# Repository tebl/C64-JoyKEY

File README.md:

# C64 JoyKEY
The *C64 JoyKEY* was born out of the desire to build my own joystick, and after having a look at the various options available I chose to build one using Cherry MX keyboard switches. They are around a dollar per piece, so after getting it all to work properly on my beloved Commodore 64 I looked into using it with a whole selection of vintage computer systems as well. There are two main versions of the *C64 JoyKEY*, the keyboard-variant already described and a board designed for use with Sanwa arcade parts instead.

With options to handle multiple types of systems comes complexity, you'll have to make a few decisions on what you want out of the *C64 JoyKEY*. Do I only want to use it as a joystick replacement on vintage systems, ideally with 2-3 fire buttons where supported? If so, then you won't need the Arduino Pro Micro.

Want to use it on a modern system as a *WASD*-style keyboard or a gamepad, then install it - a common use of these types of devices is as a macro-keyboard or a stream-deck. Note that compared to many similar solutions, the microcontroller is not required for use with any of the vintage systems - the adapters actually follow the original circuit descriptions for controllers used with the actual vintage computers. What that means is that there is truly no chance of lag added by the controller. Ever.

The pictures below show the unit when connected to my Commodore 64, including the jumper settings used with it. As I've tried to keep things as close to the standard usually associated with Atari-style joysticks, there are two joystick connectors - this is because a lot of the Commodore 64 games supported using a second joystick for specific game functions.

As with most C64 games port 2 is the one to use, port 1 is just there to connect additional fire buttons. When in doubt, just connect a cable for port 2 and you should have a good time. This was labelled after the way the controller is used on the Commodore 64. 

## Getting one
I won't be selling these, so if you want one you will probably have to build it yourself (or call your favourite friend, ideally someone with a reasonable quality soldering iron). I've created a separate documents on [building](https://github.com/tebl/C64-JoyKEY/blob/main/documentation/building.md) a *C64 JoyKEY*, this is also where you'll find the [BOM](https://github.com/tebl/C64-JoyKEY/blob/main/documentation/building.md#bom) for this project (a list of needed parts and links to where PCBs can be ordered).

* [Building C64 JoyKEY](https://github.com/tebl/C64-JoyKEY/blob/main/documentation/building.md)
* [Building C64 JoyKEY Arcade](https://github.com/tebl/C64-JoyKEY/blob/main/documentation/building_arcade.md)
* [PCBWay shared projects](https://www.pcbway.com/project/shareproject/?tag=C64%20JoyKEY)

As with all things you're soldering together by yourself, the one who soldered it takes responsibility for it. I'll try answer any opened tickets as far as I am able, but know that this is a hobby-grade project and I might be busy on spending the little energy I have on other things (be patient, check out the [schematic](https://github.com/tebl/C64-JoyKEY/tree/main/documentation/schematic) while you wait).

## Setting it up
The *C64 JoyKEY* has a handful of jumpers that need to be set correctly in order to: A - function, B - not destroy your precious vintage computer and/or consoles. The necessary details have been put into a separate [configuration](https://github.com/tebl/C64-JoyKEY/blob/main/documentation/configuration.md)-document, check it out for some information on the systems I've attempted to use the *C64 JoyKEY* with.

* [Configuring C64 JoyKEY](https://github.com/tebl/C64-JoyKEY/blob/main/documentation/configuration.md)
* [Arduino firmware](https://github.com/tebl/C64-JoyKEY/blob/main/documentation/firmware.md)

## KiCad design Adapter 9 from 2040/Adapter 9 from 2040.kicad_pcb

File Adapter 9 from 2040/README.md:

# Adapter 9 from 2040
I cant really recall the entire list of adapters that I've made of the years, but there might actually have been a few more than 9 though this is definitely the first one that I've ended up calling *Adapter 9 from 2040*. Strikingly similar in function to the [C64 Joystick Adapter](https://github.com/tebl/C64-Joystick-Adapter) that I made a while back, but given my renewed interest in the *C64 JoyKEY* via [C64 JoyKEY 2040](https://github.com/tebl/C64-JoyKEY/tree/main/C64%20Joykey%202040) it made somewhat sense to create yet another "DB-9" to USB-controller adapter.

Except this time the implementation was based on [GP2040-CE](https://gp2040-ce.info), running on a Raspberry Pi Pico variant commonly referred to as the *RP2040-Zero*. At this point quite a lot of the older Arduino-libraries have hardly seen any features added to it, but as for *GP2040-CE* - if there's a feature that you can think of, then it's probably already there in some form or another. *Adapter 9 from 2040* in its most common setup presents itself to the system you connect it to as a wired *Xbox-360 Controller*, meaning that you can use it as a controller on quite a lot of different systems.

Personally I wanted it for use with the various releases from *Retro Games Ltd.* - great little systems for playing games on when I want something that should just work, but absolutely terrible controllers. I've tested it with *TheC64 Mini*, *TheA500 Mini* and most recently *TheSpectrum* to great effect, and being able to use my vintage joysticks with them only adds to the enjoyment.

- [1> Building the device](#1-building-the-device)
- [2> Schematic](#2-schematic)
- [3> BOM](#3-bom)

# 1> Building the device
Building the device should be a straight-forward affair, you just solder the meager selection of components into place. Pay particular attention to keeping the alignment of parts somewhat straight, that's pretty much it. This documentation was written with a board that looks like the following in mind, but note that the GitHub-repository might contain changes that have yet to be tested. For that reason it is recommended that PCBs are ordered directly from the PCBWay links provided in the BOM).

Before getting started on installing actual components there are a few things that we need to cover first, and that's setting up the various jumpers found on the back of the PCB. The ones towards the bottom covers the kind of signals we want to hook up to the "DB-9"-connector, and the only one that I recommend linking is *VCC_EN* as that will be needed for quite a few of the joysticks that include a turbo-function. Takes a little bit of practice to get these to link, but if you try and get the soldering iron to heat both pads simultaniously and keep feeding in solder you'll get a perfect blob before long.

The jumpers for *B2_EN* and *B3_EN* are for controllers that have one or two extra fire buttons with a commoned ground, but as these are quite rare I'd recommend that you leave these as they are unless you specifically know what you're doing. Or in the even rarer case, is the one where you're using either [C64 Arcade](https://github.com/tebl/C64-JoyKEY/tree/main/C64%20Arcade), [C64 JoyKEY](https://github.com/tebl/C64-JoyKEY/tree/main/C64%20Joykey) or the [C64 JoyKEY 2040](https://github.com/tebl/C64-JoyKEY/tree/main/C64%20Joykey%202040).

The one case where we really need to pay attention is the ones toward the middle of the PCB, these are needed in order to specify how your *0.96" I2C OLED*-display should be wired up. The reason is that when you're ordering these from various sources they'll send you displays that were made with differing pinouts, even more annoyingly is that often you'll look at the pictures to verify that you're getting a specific revision of it - but they'll just send you a different one. Here's what the one I've jumpered for in the above picture, note specifically that *GND* is on the first pin. That means that on both jumpers we need to link pins 1-2 together (with the tiny triangle indicating pin 1). If, on the other hand, the first pin had been labelled *VCC* (or quite possibly *VDD*) the you'd instead need to link pins 2-3 for both of the jumpers. 

Moving on to actualy components that we'll be installing, I always recommend that you install things in the order of their physical height. There's not all that much that can go wrong beyond making things harder for yourself to put this one together so don't overthink things. You will however need to decide if you'll be installing the *RP2040-Zero* development board directly to the board, or with pins between the two. Before all that though, we need to talk about what a *RP2040-Zero* actually is. And here's a couple of them that you might encounter while shopping around: 

Both of these are smaller versions of the *Raspberry Pi Pico* boards that come directly from the *Raspberry Pi Foundation*, but they're running the same chip so you essentially get the same amount of computational power - just with slightly less pins, and in a significantly smaller package. Confusingly this isn't a *Raspberry Pi* as the single-board computers (*SBC*) that came before it, this is a somewhat new line of microcontrollers similar to the *Arduino* or *ESP-32*. As for the boards above, the first one is from a vendor called *Waveshare* and this is the version that you'll encounter on more reputed sites for purchasing electrical components. The other is a clone that normally works just as well, just at half the price and without any expectation that all of were put together like they should - so buy at least two of them in case one blows up!

Here I've skipped over the difficult parts and soldered it into place. In order to get the alignment just right I tend to insert pin headers through both boards on at least two of the sides, then position it just right and solder one pin into place. If it all looks right, you can go ahead and remove the pin headers before soldering the rest. It might take some getting used to soldering things together like this if you're not used to it, but just try and get the soldering iron to touch both pads at the same time then feed in the solder until it forms a shiny avalanche.

If you're going to install a faceplate on the adapter, then you're going to need a set of standoffs in each of the four corners. These need to have a height of 6mm, they're fixed in place with similar nuts on the underside. You might also use some that are slightly longer, but keep in mind that we need to have enough of a reach on the pin headers on your OLED to match - switches also need to be tall enough to poke through all of it. On second thought, just go with 6mm and we'll move on from there.

Next up is the *right-angle "DB-9" male connector* that I keep buying off of the regular sites, and I believe it's a clone of an RND-part, but don't hold me to that. If you look for the a connector that looks like this on the pictures, then you'll get the correct one. It snaps into place on the board and solders in well enough, just keep your fingers away from the metal as it heats up quite quickly when soldering. I've literally burned myself on them several times. And at the time of writing, this is probably the first time I've used the word "literally" correctly. I hope. 

The next step is all of the switches, and here I've inserted them all into place and temporarily installed the faceplate. Doing it in this order ensures that the switch ends up sitting correctly, and won't be rubbing too much against the cutouts in the faceplate. Once satisfied with all of that, you can go ahead and solder in the switches. Just do one of the pins at first, then recheck to make sure it hasn't popped out or gone wonky on you in the meantime (ask me how I know).

As for my next trick on my list of things I've just done without much to actually show you, I've gone ahead and added the display. Previously on this episode of putting things together with our fiery stick of endless ouchies (also known as a soldering iron), we lamented the state lack of real part numbers for things like displays. Clones taking liberties when shamelessly copying other clones, enabling people like me to actually own a whole bunch of them and so on. The board will take just about any *0.96" I2C OLED*-display, but you'll need to ensure that you order specific ones if you want the cutouts on the faceplates to line up just perfectly. Currently there is only one available, [FaceplateB](https://github.com/tebl/C64-JoyKEY/tree/main/faceplates/Adapter%209%20FaceplateB) - this one was designed for the *New* displays available in all the usual places. Technically it's actually the new *New* display, but who's counting - at least one identifying trait is that they're the first generation that came with yellow as colour.

There are holes for orienting it correctly, but before even considering soldering anything - take a look at how it looks with the faceplate in place. We need to ensure that it sits flush against the inside edge of the faceplate, and while you could glue the foam that often comes around the pins directly to the PCB to push it upwards - I prefer adding a bunch of layers of double-sided foam tape. Just don't go overboard -  we want it to push the glass up against the PCB, not shatter the whole thing from extreme pressure. If you need to reorient it a bit, you can poke a screwdriver into the mounting holes from the back and adjust it that way. Once satisfied with your rough placement, solder a single pin. Recheck. Recheck. Recheck. And then solder the rest.

Once satisfied with all of it, make yourself a cup of tea, soup or whatever you want - you're buying anyway! Once back to the table, you need to take the faceplate back off again, as we need access to the buttons directly on the *RP2040-Zero* when installing *GP2040-CE*, but that's all covered in a completely different document - [From Zero to GP2040](https://github.com/tebl/C64-JoyKEY/blob/main/documentation/gp2040_zero.md).

# 2> Schematic
The supplied KiCad files should be sufficient as both a schematic and as a  starting point for ordering PCBs (basically you could just zip the contents of the export folder and upload that on a fabrication site), the schematic is also available in [PDF-format](https://github.com/tebl/C64-JoyKEY/tree/main/documentation/schematic) and this is what you'll need to print and work your way through when things fail to work as expected.

# 3> BOM
Most parts should be easy to get a hold of from all of the regular places, just not any of the incredibly reputable ones. Which is why things usually cost a third of what they cost elsewhere, but you need to buy two in order to ensure that at least one works. I get most of my components from AliExpress though I hear nice things about the wheel of fortune thingie, but they sent one too many notifications so they're banned in my household.

I'd really like for you to have a nice and clear BOM with consistent part numbers from actual reputable sites, but I can't even afford their shipping options so it is what it is - mostly hints at what to search for and how many you need. If a counted part is listed in a parenthesis, then you don't strictly need that part though it's all cheap enough that you probably count on buying them anyway.

| Reference        | Item                                                              | Count | Order  |
| -----------------| ----------------------------------------------------------------- | ----- | ------ |
| PCB              | Fabricate using Gerber files                                      |     1 | [PCBWay](https://www.pcbway.com/project/shareproject/Adapter_9_from_2040_578739f8.html)
| PCB (Faceplate B)| Fabricate using Gerber files                                      |    (1)| [PCBWay](https://www.pcbway.com/project/shareproject/Adapter_9_from_2040_Faceplate_B_dc748e4f.html)
| IC1 *            | 0.96" I2C OLED display 128x64 (New variant reqd. for FaceplateB)) |    (1)|
| J1               | Male DB-9 right-angle connector (usually listed as PCB-mount)     |     1 |
| SW1-SW8          | 6x6x10mm tactile switch ("DIP-4")                                 |    (8)|
| U1               | Raspberry Pi Pico (RP2040-Zero)                                   |     1 |
| **               | M3 nylon nut                                                      |    (4)|
| **               | M3x6+6mm nylon hex standoff                                       |    (4)|
| **               | M3x6mm nylon screw                                                |    (4)|

*) See text for construction for hints on purchasing the correct variant to go with a specific faceplate, when in doubt order several and use the one that fits.

**) These components are for the additional faceplate. Strictly not necessary, but keeps the  whole setup looking as stylish as it can be. The faceplate is reversible, so install it in the orientation that you'd like.

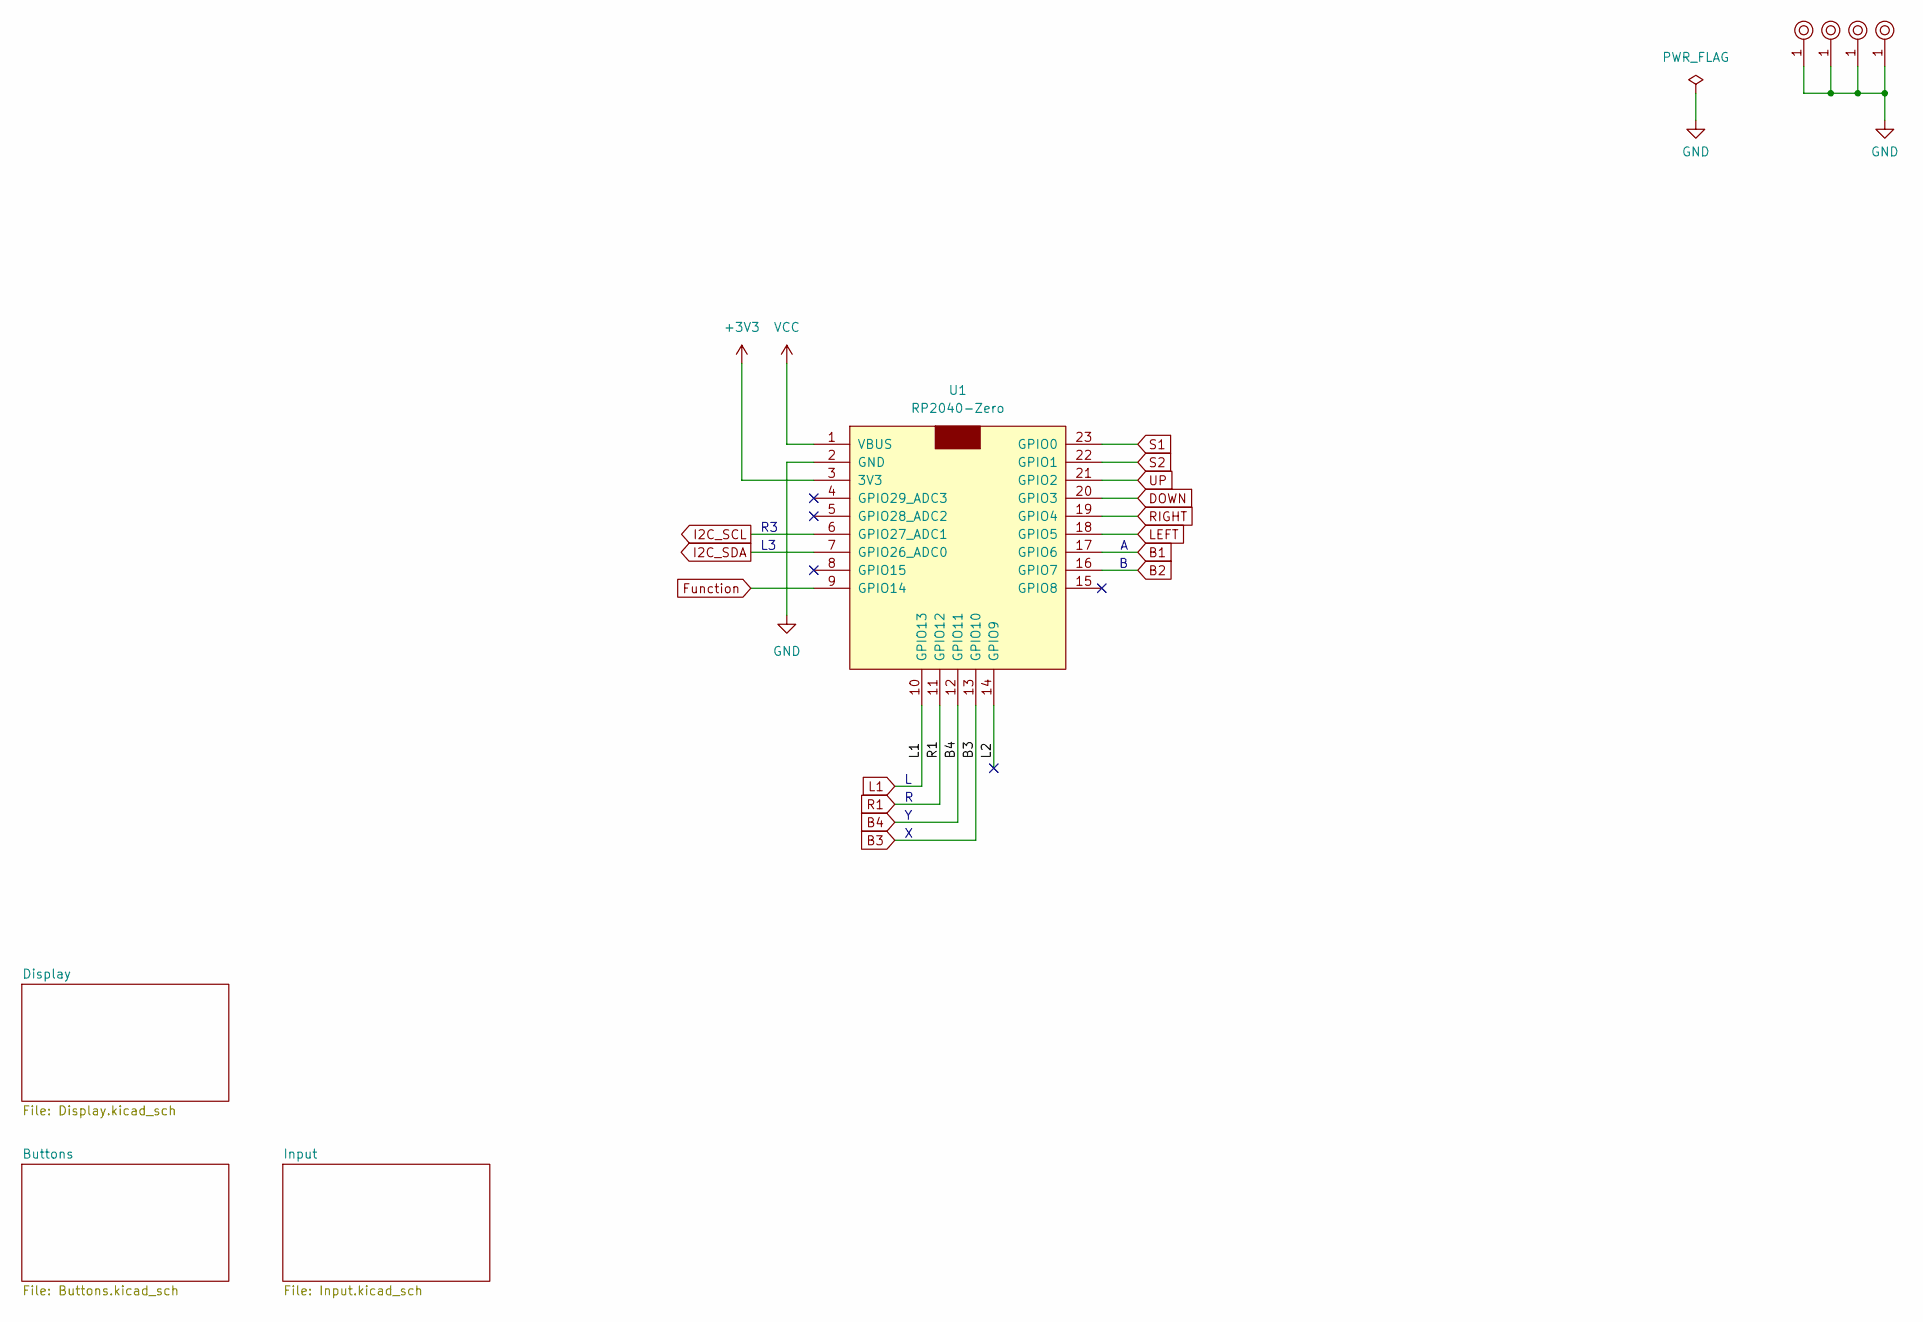
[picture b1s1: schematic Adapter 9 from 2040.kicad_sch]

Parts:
M1, M2, M3, M4: Mounting; M3_pin
U1: RP2040-Zero; RP2040-Zero_Clean

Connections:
+3V3: U1.3 (3V3); also elsewhere on the board
/L2: U1.14 (GPIO9)
/L2_1: U1.14 (GPIO9)
B1: U1.17 (GPIO6); also elsewhere on the board
B2: U1.16 (GPIO7); also elsewhere on the board
B3: U1.13 (GPIO10); also elsewhere on the board
B4: U1.12 (GPIO11); also elsewhere on the board
DOWN: U1.20 (GPIO3); also elsewhere on the board
Function: U1.9 (GPIO14); also elsewhere on the board
GND: M1.1, M2.1, M3.1, M4.1, U1.2 (GND); also elsewhere on the board
I2C_SCL: U1.6 (GPIO27_ADC1); also elsewhere on the board
I2C_SDA: U1.7 (GPIO26_ADC0); also elsewhere on the board
L1: U1.10 (GPIO13); also elsewhere on the board
LEFT: U1.18 (GPIO5); also elsewhere on the board
R1: U1.11 (GPIO12); also elsewhere on the board
RIGHT: U1.19 (GPIO4); also elsewhere on the board
S1: U1.23 (GPIO0); also elsewhere on the board
S2: U1.22 (GPIO1); also elsewhere on the board
UP: U1.21 (GPIO2); also elsewhere on the board
VCC: U1.1 (VBUS); also elsewhere on the board

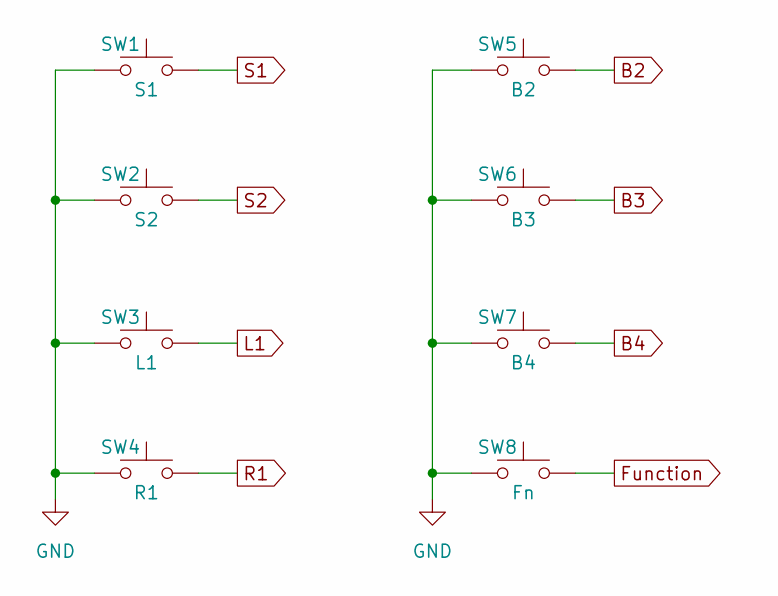
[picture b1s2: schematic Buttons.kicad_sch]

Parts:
SW1: S1; SW_PUSH_6mm
SW2: S2; SW_PUSH_6mm
SW3: L1; SW_PUSH_6mm
SW4: R1; SW_PUSH_6mm
SW5: B2; SW_PUSH_6mm
SW6: B3; SW_PUSH_6mm
SW7: B4; SW_PUSH_6mm
SW8: Fn; SW_PUSH_6mm

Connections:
B2: SW5.1; also elsewhere on the board
B3: SW6.1; also elsewhere on the board
B4: SW7.1; also elsewhere on the board
Function: SW8.1; also elsewhere on the board
GND: SW1.2, SW2.2, SW3.2, SW4.2, SW5.2, SW6.2, SW7.2, SW8.2; also elsewhere on the board
L1: SW3.1; also elsewhere on the board
R1: SW4.1; also elsewhere on the board
S1: SW1.1; also elsewhere on the board
S2: SW2.1; also elsewhere on the board

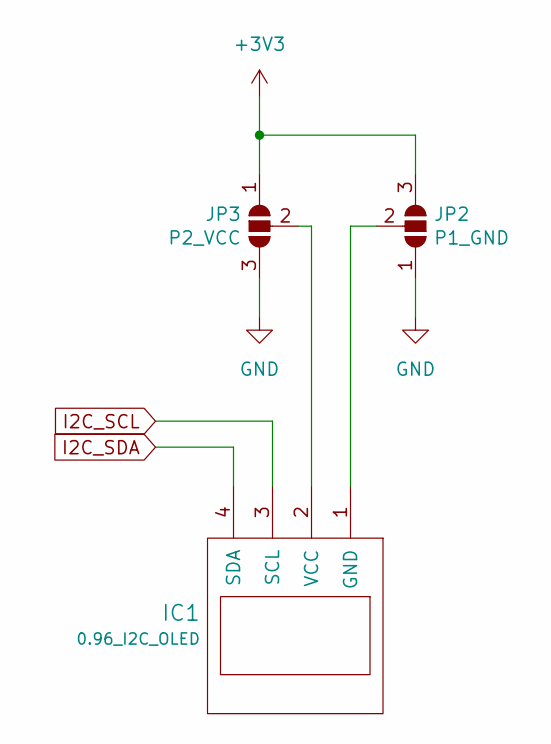
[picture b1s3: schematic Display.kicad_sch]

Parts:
IC1: 0.96_I2C_OLED; 0.96_I2C_OLED_NEW_Top
JP2: P1_GND; SolderJumper-3_P1.3mm_Open_Pad1.0x1.5mm
JP3: P2_VCC; SolderJumper-3_P1.3mm_Open_Pad1.0x1.5mm

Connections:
+3V3: JP2.3 (B), JP3.1 (A); also elsewhere on the board
GND: JP2.1 (A), JP3.3 (B); also elsewhere on the board
I2C_SCL: IC1.3 (SCL); also elsewhere on the board
I2C_SDA: IC1.4 (SDA); also elsewhere on the board
unnamed: IC1.1 (GND), JP2.2 (C)
unnamed: IC1.2 (VCC), JP3.2 (C)

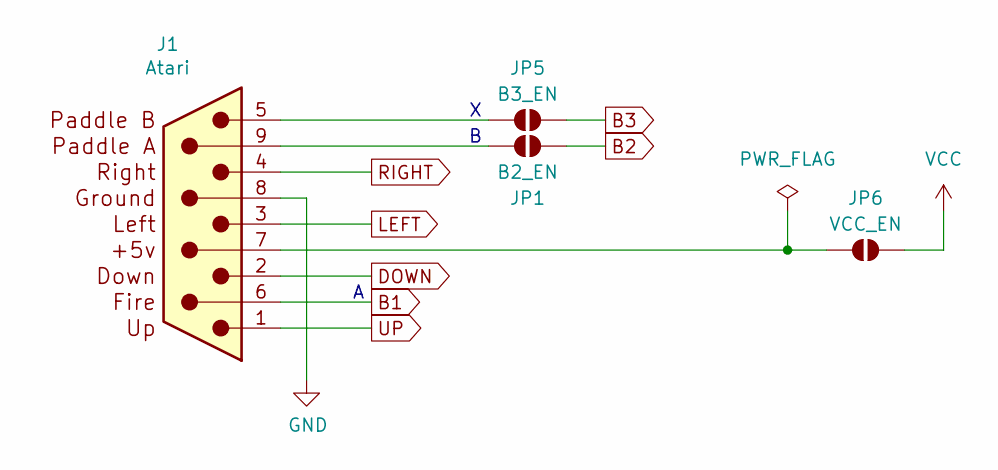
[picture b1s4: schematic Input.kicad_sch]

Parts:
J1: Atari; DSUB-9_Male_Horizontal_P2.77x2.84mm_EdgePinOffset7.70mm_Hou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
JP1: B2_EN; bridge
JP5: B3_EN; bridge
JP6: VCC_EN; bridge

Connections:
B1: J1.6; also elsewhere on the board
B2: JP1.2 (B); also elsewhere on the board
B3: JP5.2 (B); also elsewhere on the board
DOWN: J1.2; also elsewhere on the board
GND: J1.8 (GND); also elsewhere on the board
LEFT: J1.3; also elsewhere on the board
unnamed: J1.7 (VCC), JP6.1 (A)
unnamed: J1.9, JP1.1 (A)
unnamed: J1.5, JP5.1 (A)
RIGHT: J1.4; also elsewhere on the board
UP: J1.1; also elsewhere on the board
VCC: JP6.2 (B); also elsewhere on the board

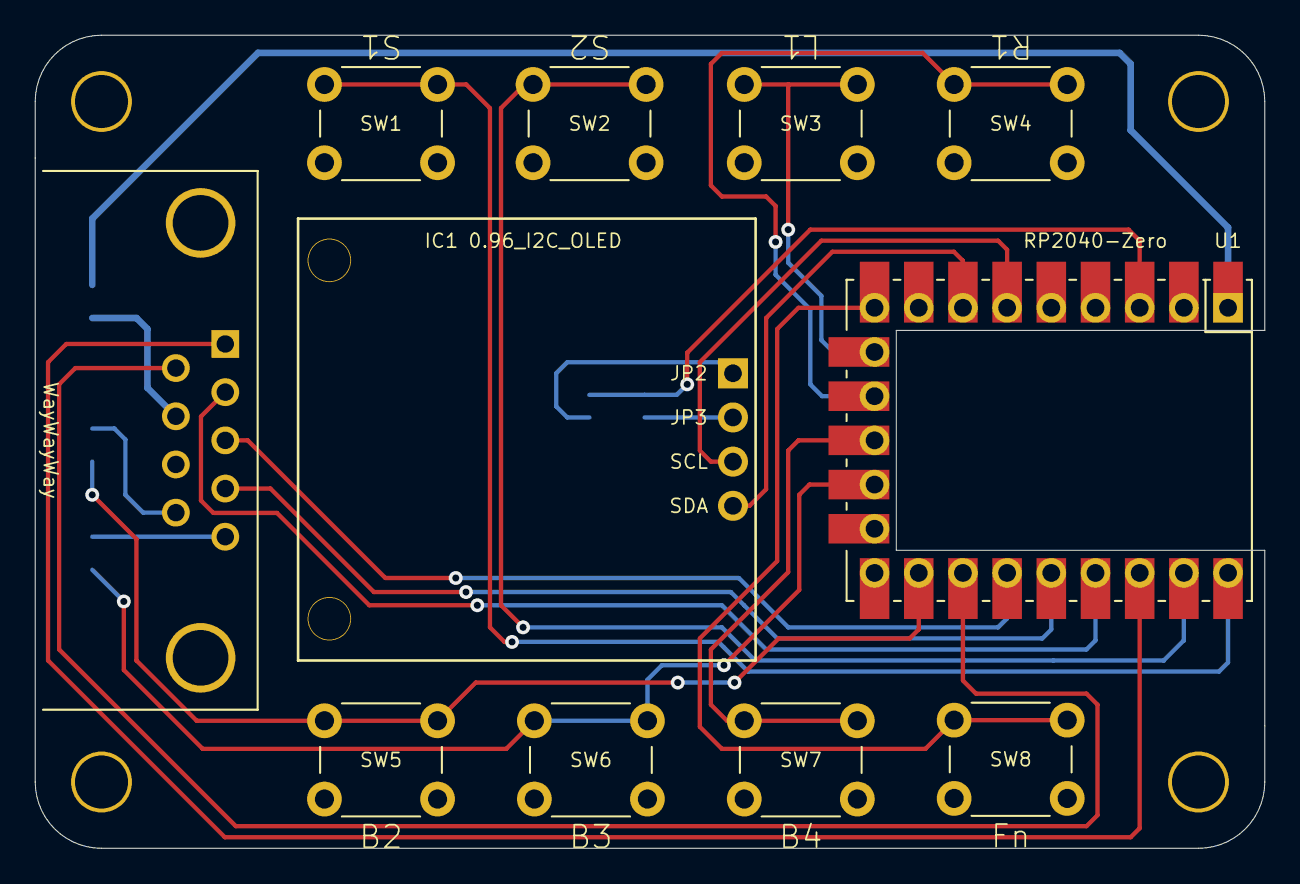
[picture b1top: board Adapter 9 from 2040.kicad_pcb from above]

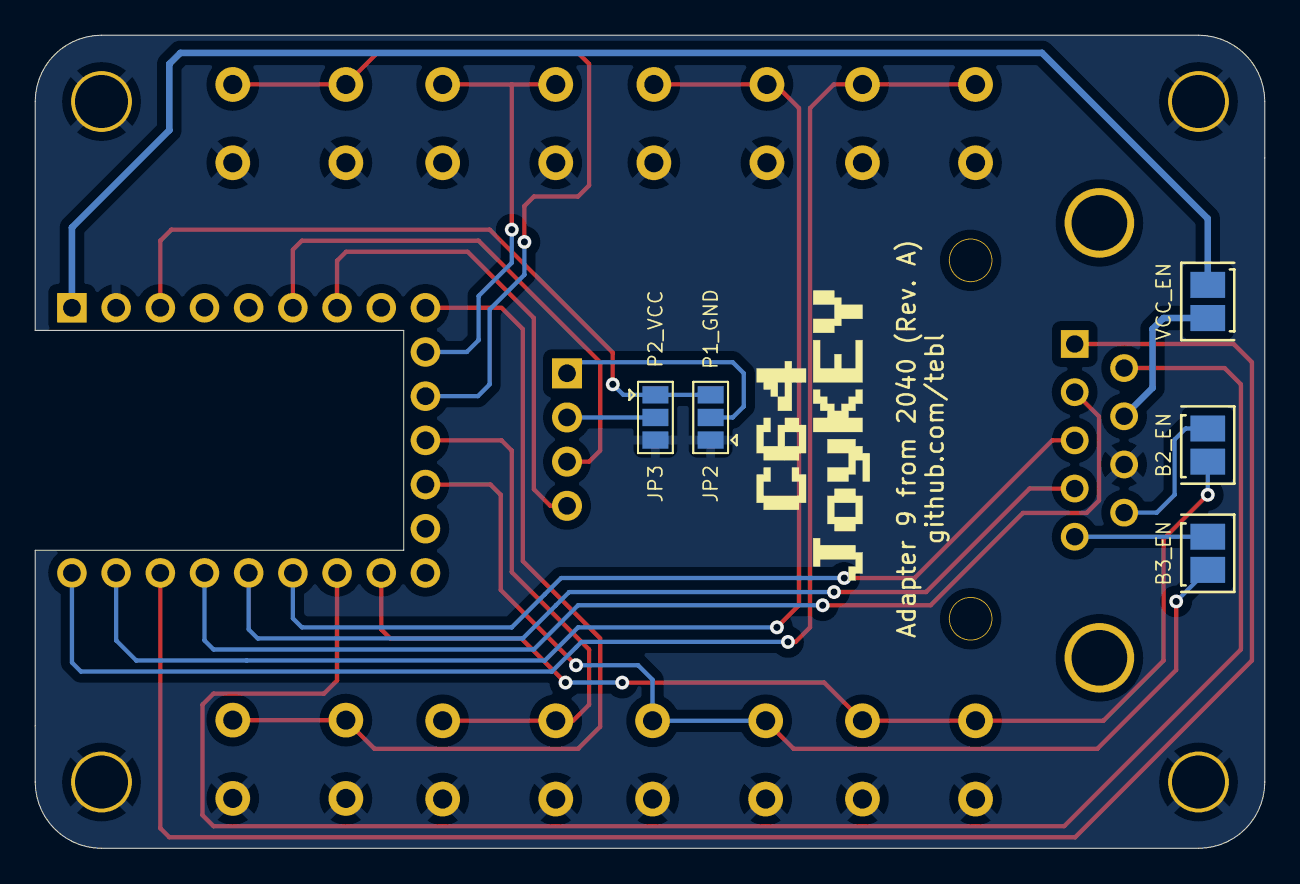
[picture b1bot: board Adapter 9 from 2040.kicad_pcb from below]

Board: 2 copper layers, 70.7 x 46.7 mm, 20 parts (5 on the bottom side), 23 nets.

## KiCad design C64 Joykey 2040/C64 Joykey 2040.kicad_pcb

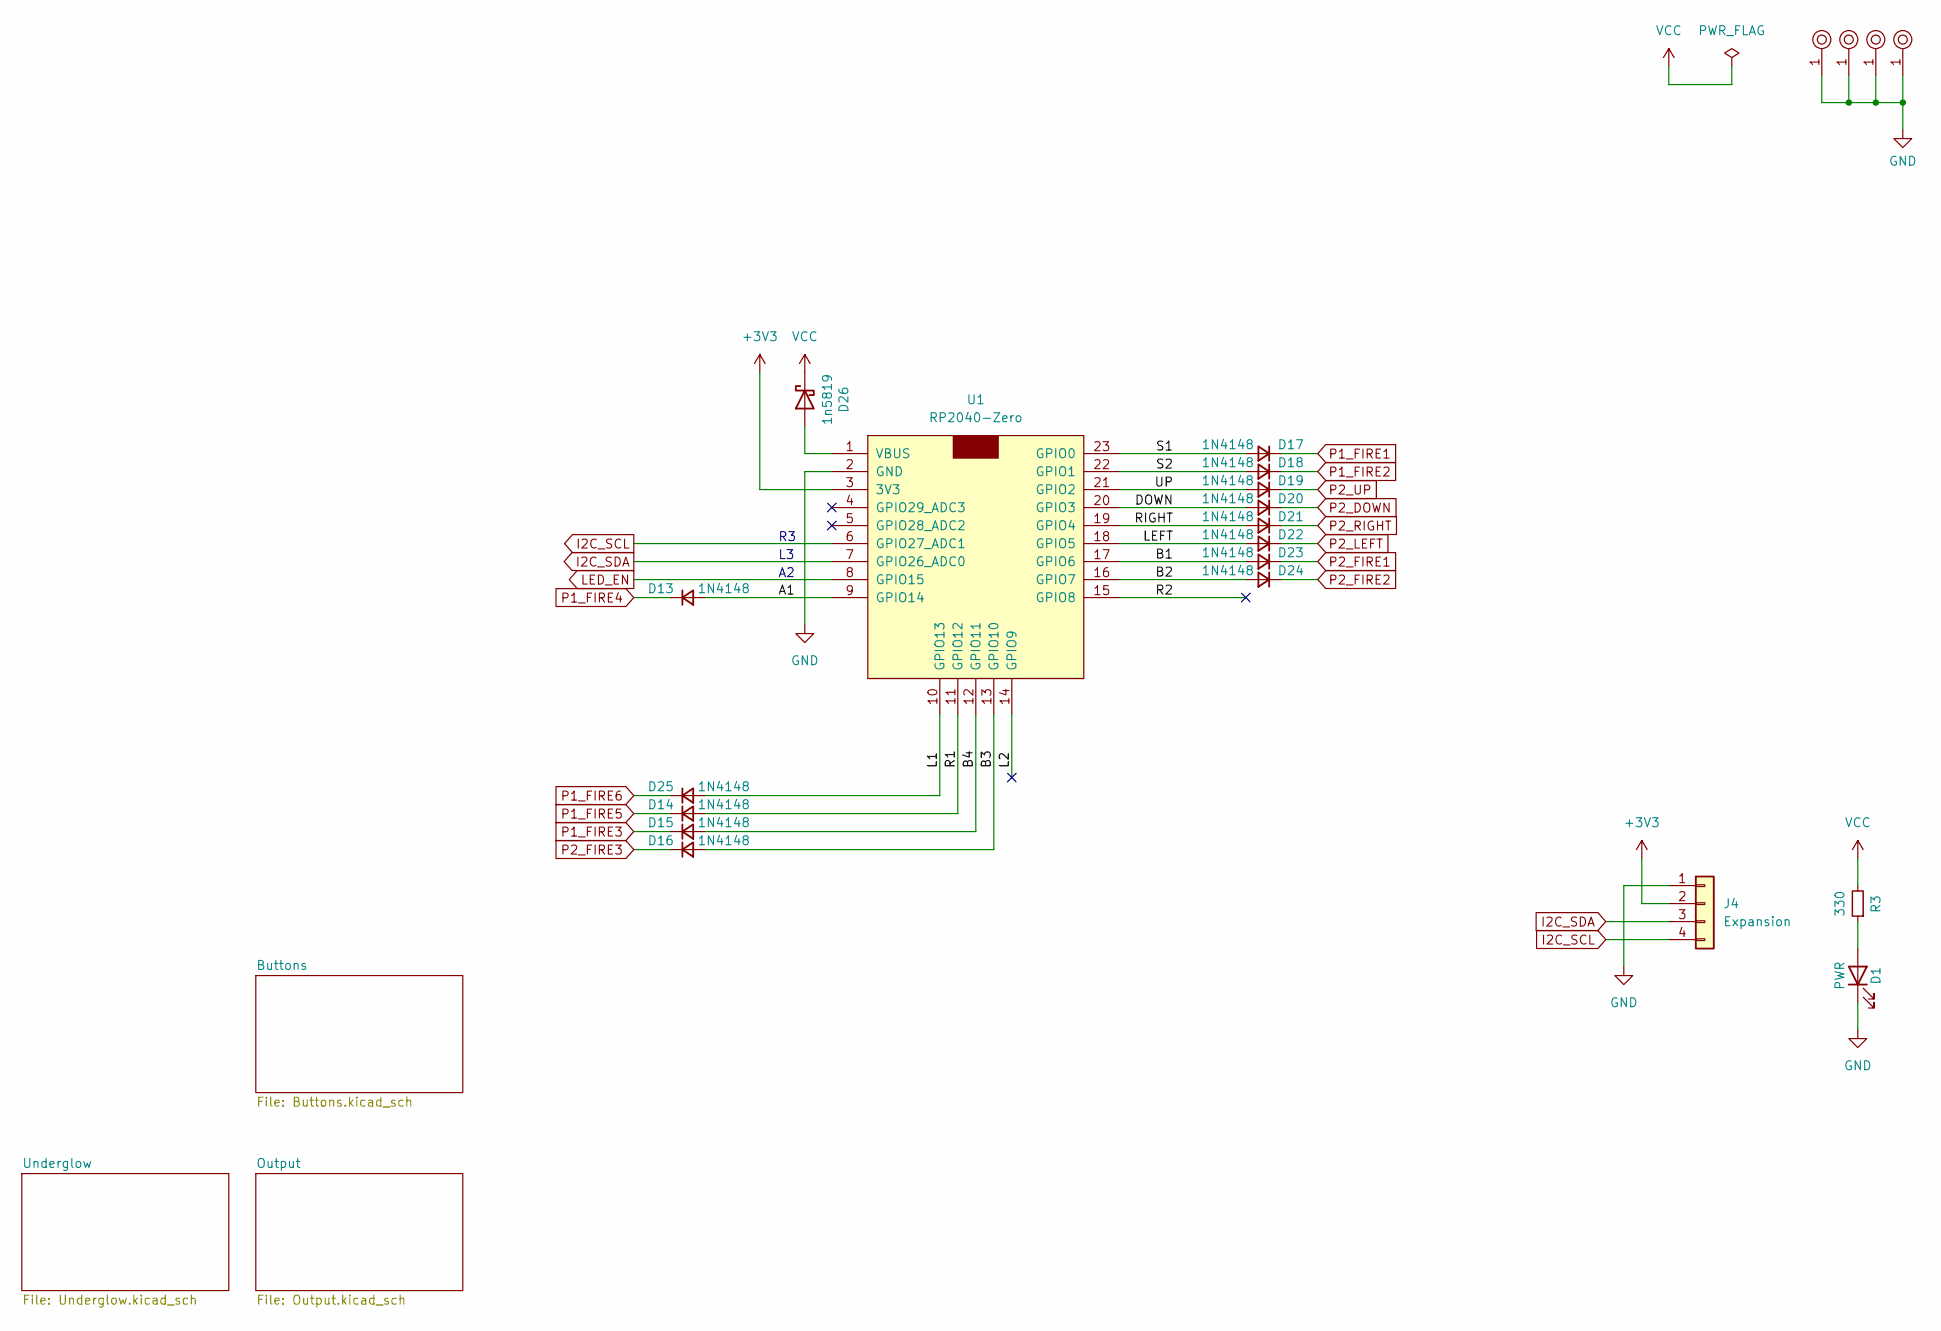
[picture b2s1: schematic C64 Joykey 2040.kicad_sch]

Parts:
D1: PWR; LED_D5.0mm
D13, D14, D15, D16, D17, D18, D19, D20, D21, D22, D23, D24, D25: 1N4148; D_DO-35_SOD27_P7.62mm_Horizontal
D26: 1n5819; D_DO-41_SOD81_P10.16mm_Horizontal
J4: Expansion; JST_XH_B4B-XH-A_1x04_P2.50mm_Right_Angle
M1, M2, M3, M4: Mounting; M3_pin
R3: 330; R_Axial_DIN0207_L6.3mm_D2.5mm_P10.16mm_Horizontal
U1: RP2040-Zero; RP2040-Zero-THT

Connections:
+3V3: J4.2, U1.3 (3V3)
/A1: D13.2 (A), U1.9 (GPIO14)
/B1: D23.2 (A), U1.17 (GPIO6)
/B2: D24.2 (A), U1.16 (GPIO7)
/B3: D16.2 (A), U1.13 (GPIO10)
/B4: D15.2 (A), U1.12 (GPIO11)
/DOWN: D20.2 (A), U1.20 (GPIO3)
/L1: D25.2 (A), U1.10 (GPIO13)
/L2: U1.14 (GPIO9)
/LEFT: D22.2 (A), U1.18 (GPIO5)
/R1: D14.2 (A), U1.11 (GPIO12)
/R2: U1.15 (GPIO8)
/RIGHT: D21.2 (A), U1.19 (GPIO4)
/S1: D17.2 (A), U1.23 (GPIO0)
/S2: D18.2 (A), U1.22 (GPIO1)
/UP: D19.2 (A), U1.21 (GPIO2)
GND: D1.1 (K), J4.1, M1.1, M2.1, M3.1, M4.1, U1.2 (GND); also elsewhere on the board
I2C_SCL: J4.4, U1.6 (GPIO27_ADC1)
I2C_SDA: J4.3, U1.7 (GPIO26_ADC0)
LED_EN: U1.8 (GPIO15); also elsewhere on the board
unnamed: D1.2 (A), R3.1
unnamed: D26.2 (A), U1.1 (VBUS)
P1_FIRE1: D17.1 (K); also elsewhere on the board
P1_FIRE2: D18.1 (K); also elsewhere on the board
P1_FIRE3: D15.1 (K); also elsewhere on the board
P1_FIRE4: D13.1 (K); also elsewhere on the board
P1_FIRE5: D14.1 (K); also elsewhere on the board
P1_FIRE6: D25.1 (K); also elsewhere on the board
P2_DOWN: D20.1 (K); also elsewhere on the board
P2_FIRE1: D23.1 (K); also elsewhere on the board
P2_FIRE2: D24.1 (K); also elsewhere on the board
P2_FIRE3: D16.1 (K); also elsewhere on the board
P2_LEFT: D22.1 (K); also elsewhere on the board
P2_RIGHT: D21.1 (K); also elsewhere on the board
P2_UP: D19.1 (K); also elsewhere on the board
VCC: D26.1 (K), R3.2; also elsewhere on the board

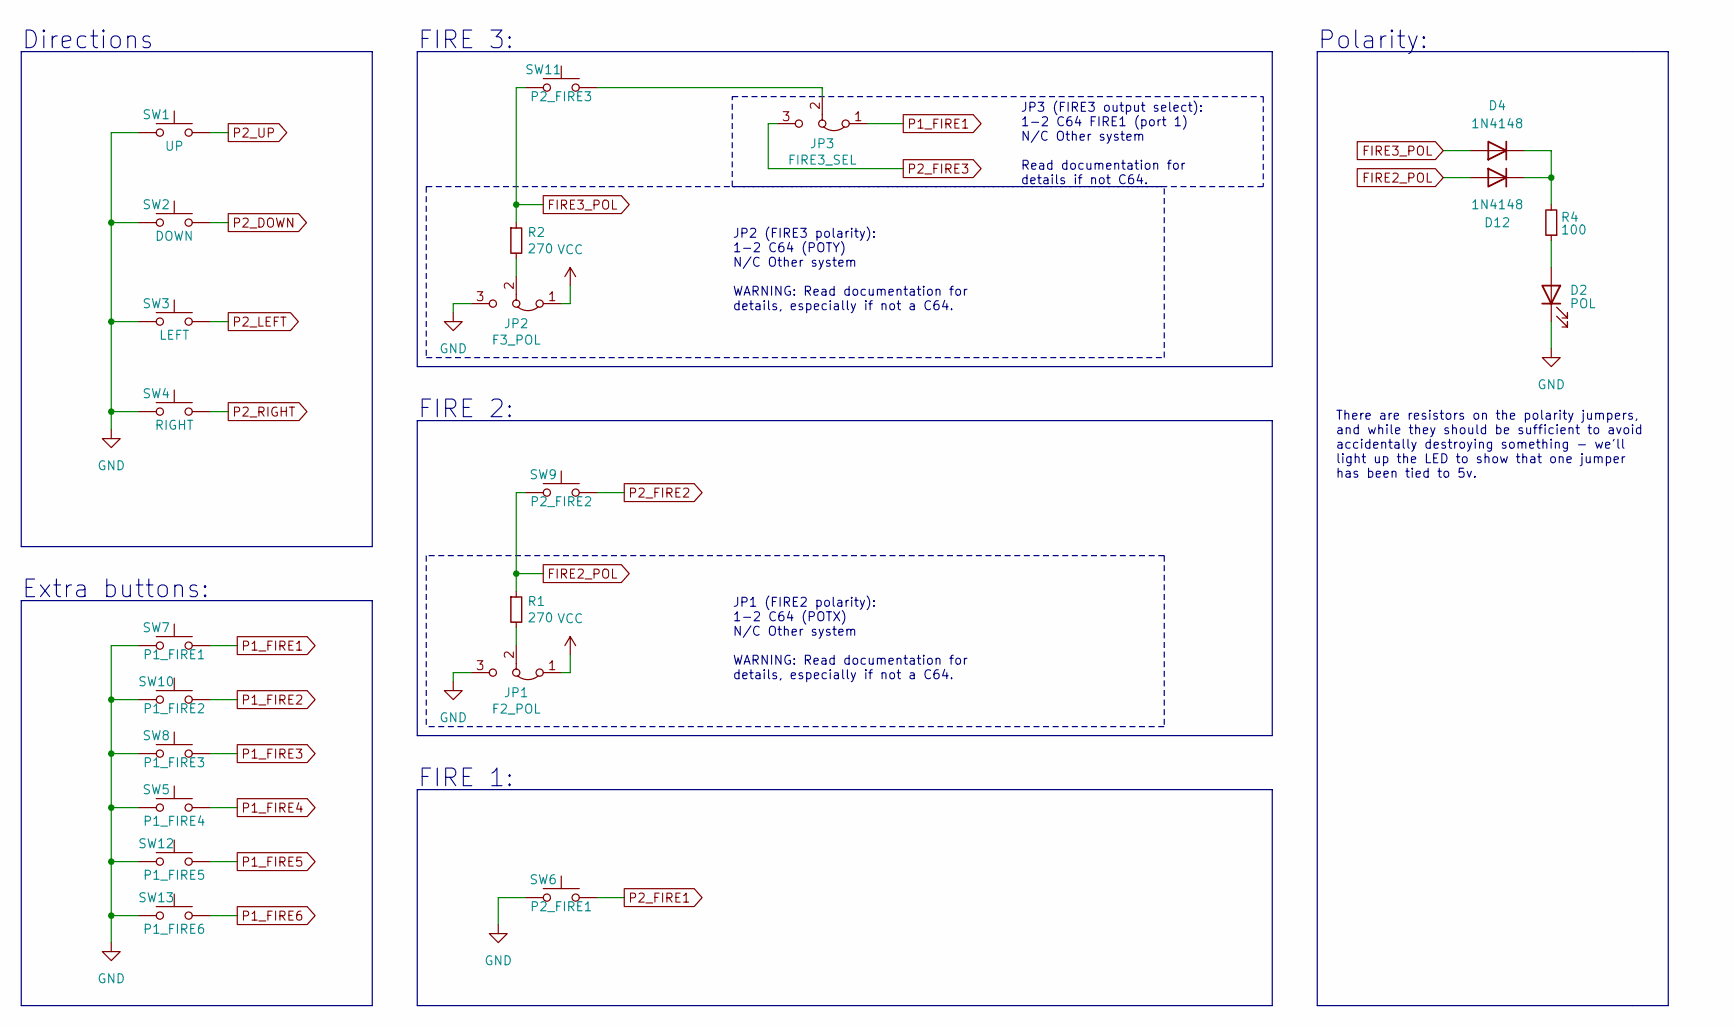
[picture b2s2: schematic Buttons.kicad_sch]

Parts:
D2: POL; LED_D5.0mm
D4, D12: 1N4148; D_DO-35_SOD27_P7.62mm_Horizontal
JP1: F2_POL; PinHeader_1x03_P2.54mm_Horizontal
JP2: F3_POL; PinHeader_1x03_P2.54mm_Horizontal
JP3: FIRE3_SEL; PinHeader_1x03_P2.54mm_Horizontal
R1, R2: 270; R_Axial_DIN0207_L6.3mm_D2.5mm_P10.16mm_Horizontal
R4: 100; R_Axial_DIN0207_L6.3mm_D2.5mm_P10.16mm_Horizontal
SW1: UP; SW_Cherry_MX_1.00u_PCB
SW2: DOWN; SW_Cherry_MX_1.00u_PCB
SW3: LEFT; SW_Cherry_MX_1.00u_PCB
SW4: RIGHT; SW_Cherry_MX_1.00u_PCB
SW5: P1_FIRE4; SW_Tactile_SPST_Angled_PTS645Vx31-2LFS
SW6: P2_FIRE1; SW_Cherry_MX_1.00u_PCB
SW7: P1_FIRE1; SW_Tactile_SPST_Angled_PTS645Vx31-2LFS
SW8: P1_FIRE3; SW_Tactile_SPST_Angled_PTS645Vx31-2LFS
SW9: P2_FIRE2; SW_Cherry_MX_1.00u_PCB
SW10: P1_FIRE2; SW_Tactile_SPST_Angled_PTS645Vx31-2LFS
SW11: P2_FIRE3; SW_Cherry_MX_1.00u_PCB
SW12: P1_FIRE5; SW_Tactile_SPST_Angled_PTS645Vx31-2LFS
SW13: P1_FIRE6; SW_Tactile_SPST_Angled_PTS645Vx31-2LFS

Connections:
FIRE2_POL: D12.2 (A), R1.1, SW9.2
FIRE3_POL: D4.2 (A), R2.1, SW11.2
GND: D2.1 (K), JP1.3 (B), JP2.3 (B), SW1.2, SW2.2, SW3.2, SW4.2, SW5.2, SW6.2, SW7.2, SW8.2, SW10.2, SW12.2, SW13.2; also elsewhere on the board
unnamed: D2.2 (A), R4.1
unnamed: D4.1 (K), D12.1 (K), R4.2
unnamed: JP1.2 (C), R1.2
unnamed: JP2.2 (C), R2.2
unnamed: JP3.2 (C), SW11.1
P1_FIRE1: JP3.1 (A), SW7.1; also elsewhere on the board
P1_FIRE2: SW10.1; also elsewhere on the board
P1_FIRE3: SW8.1; also elsewhere on the board
P1_FIRE4: SW5.1; also elsewhere on the board
P1_FIRE5: SW12.1; also elsewhere on the board
P1_FIRE6: SW13.1; also elsewhere on the board
P2_DOWN: SW2.1; also elsewhere on the board
P2_FIRE1: SW6.1; also elsewhere on the board
P2_FIRE2: SW9.1; also elsewhere on the board
P2_FIRE3: JP3.3 (B); also elsewhere on the board
P2_LEFT: SW3.1; also elsewhere on the board
P2_RIGHT: SW4.1; also elsewhere on the board
P2_UP: SW1.1; also elsewhere on the board
VCC: JP1.1 (A), JP2.1 (A); also elsewhere on the board

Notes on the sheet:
FIRE 1:
JP2 (FIRE3 polarity): 1-2 C64 (POTY) N/C Other system WARNING: Read documentation for details, especially if not a C64.
There are resistors on the polarity jumpers, and while they should be sufficient to avoid accidentally destroying something - we'll light up the LED to show that one jumper has been tied to 5v.
JP1 (FIRE2 polarity): 1-2 C64 (POTX) N/C Other system WARNING: Read documentation for details, especially if not a C64.
Directions
FIRE 3:
Extra buttons:
FIRE 2:
Polarity:
JP3 (FIRE3 output select): 1-2 C64 FIRE1 (port 1) N/C Other system Read documentation for details if not C64.

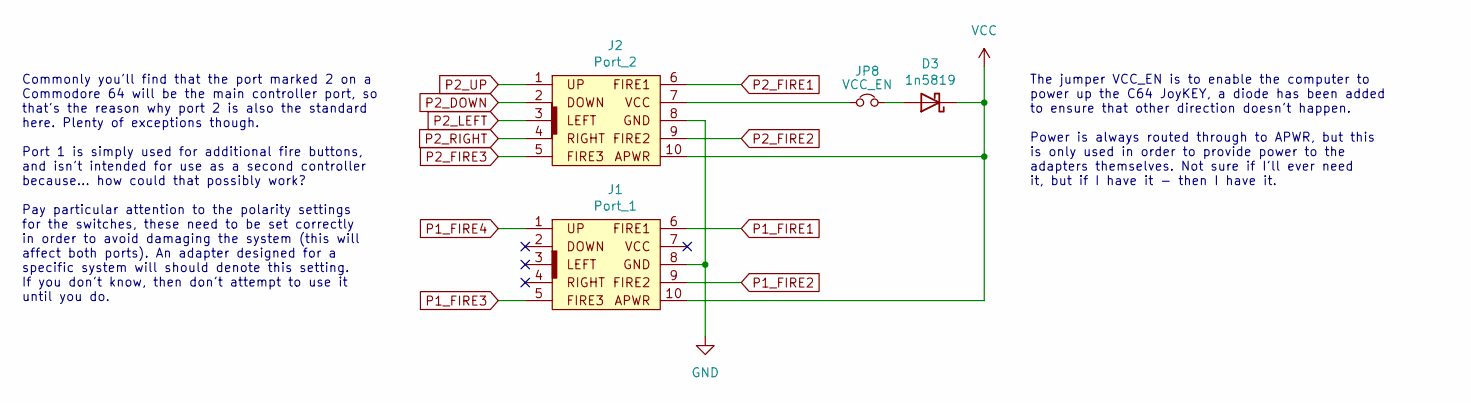
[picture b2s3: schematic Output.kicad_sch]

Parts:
D3: 1n5819; D_DO-41_SOD81_P10.16mm_Horizontal
J1: Port_1; IDC_Joystick
J2: Port_2; IDC_Joystick
JP8: VCC_EN; PinHeader_1x02_P2.54mm_Vertical

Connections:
GND: J1.8, J2.8; also elsewhere on the board
unnamed: D3.2 (A), JP8.2
unnamed: J2.7, JP8.1
P1_FIRE1: J1.6; also elsewhere on the board
P1_FIRE2: J1.9; also elsewhere on the board
P1_FIRE3: J1.5; also elsewhere on the board
P1_FIRE4: J1.1; also elsewhere on the board
P2_DOWN: J2.2; also elsewhere on the board
P2_FIRE1: J2.6; also elsewhere on the board
P2_FIRE2: J2.9; also elsewhere on the board
P2_FIRE3: J2.5; also elsewhere on the board
P2_LEFT: J2.3; also elsewhere on the board
P2_RIGHT: J2.4; also elsewhere on the board
P2_UP: J2.1; also elsewhere on the board
VCC: D3.1 (K), J1.10 (EX_VCC), J2.10 (EX_VCC); also elsewhere on the board

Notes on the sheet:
Commonly you'll find that the port marked 2 on a Commodore 64 will be the main controller port, so that's the reason why port 2 is also the standard here. Plenty of exceptions though. Port 1 is simply used for additional fire buttons, and isn't intended for use as a second controller because... how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
The jumper VCC_EN is to enable the computer to power up the C64 JoyKEY, a diode has been added to ensure that other direction doesn't happen. Power is always routed through to APWR, but this is only used in order to provide power to the adapters themselves. Not sure if I'll ever need it, but if I h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

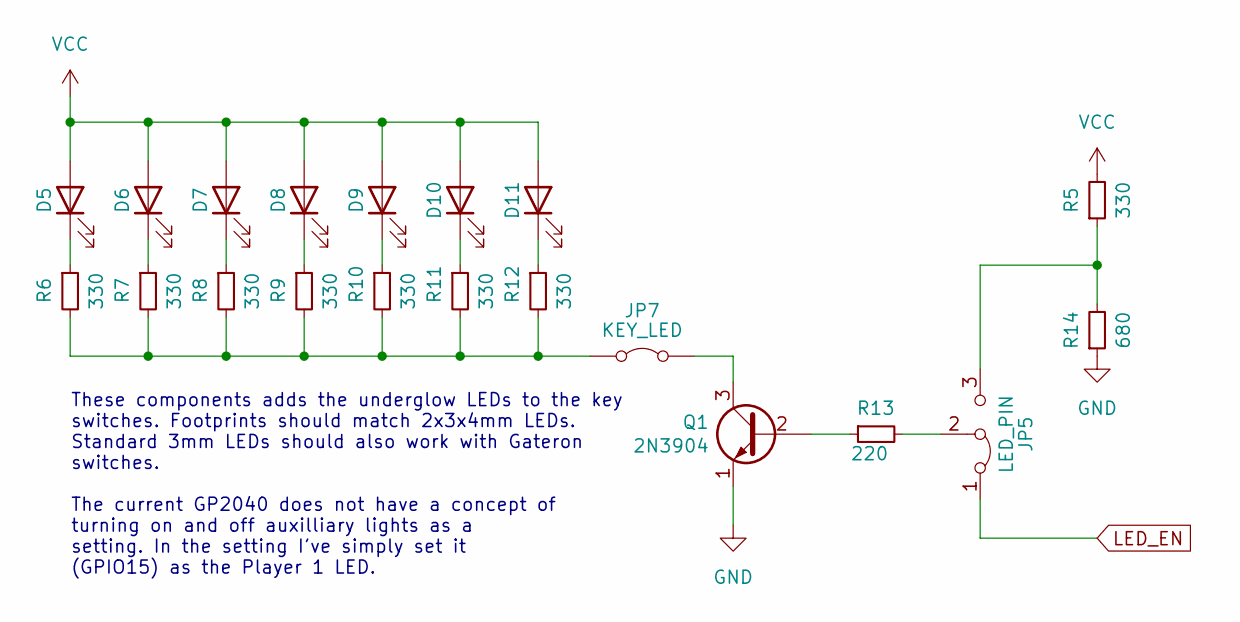
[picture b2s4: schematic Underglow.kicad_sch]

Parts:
D5, D6, D7, D8, D9, D10, D11: LED; LED_Rectangular_W3.0mm_H2.0mm
JP5: LED_PIN; PinHeader_1x03_P2.54mm_Vertical
JP7: KEY_LED; PinHeader_1x02_P2.54mm_Horizontal
Q1: 2N3904; TO-92_Inline_Wide
R5, R6, R7, R8, R9, R10, R11, R12: 330; R_Axial_DIN0207_L6.3mm_D2.5mm_P10.16mm_Horizontal
R13: 220; R_Axial_DIN0207_L6.3mm_D2.5mm_P10.16mm_Horizontal
R14: 680; R_Axial_DIN0207_L6.3mm_D2.5mm_P10.16mm_Horizontal

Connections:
GND: Q1.1 (E), R14.1; also elsewhere on the board
LED_EN: JP5.1 (A); also elsewhere on the board
unnamed: D5.1 (K), R6.1
unnamed: D6.1 (K), R7.1
unnamed: D7.1 (K), R8.1
unnamed: D8.1 (K), R9.1
unnamed: D9.1 (K), R10.1
unnamed: D10.1 (K), R11.1
unnamed: D11.1 (K), R12.1
unnamed: JP5.3 (B), R5.1, R14.2
unnamed: JP5.2 (C), R13.2
unnamed: JP7.1 (A), R6.2, R7.2, R8.2, R9.2, R10.2, R11.2, R12.2
unnamed: JP7.2 (B), Q1.3 (C)
unnamed: Q1.2 (B), R13.1
VCC: D5.2 (A), D6.2 (A), D7.2 (A), D8.2 (A), D9.2 (A), D10.2 (A), D11.2 (A), R5.2; also elsewhere on the board

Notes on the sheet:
These components adds the underglow LEDs to the key switches. Footprints should match 2x3x4mm LEDs. Standard 3mm LEDs should also work with Gateron switches. The current GP2040 does not have a concept of turning on and off auxilliary lights as a setting. In the setting I've simply set it (GPIO15) a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

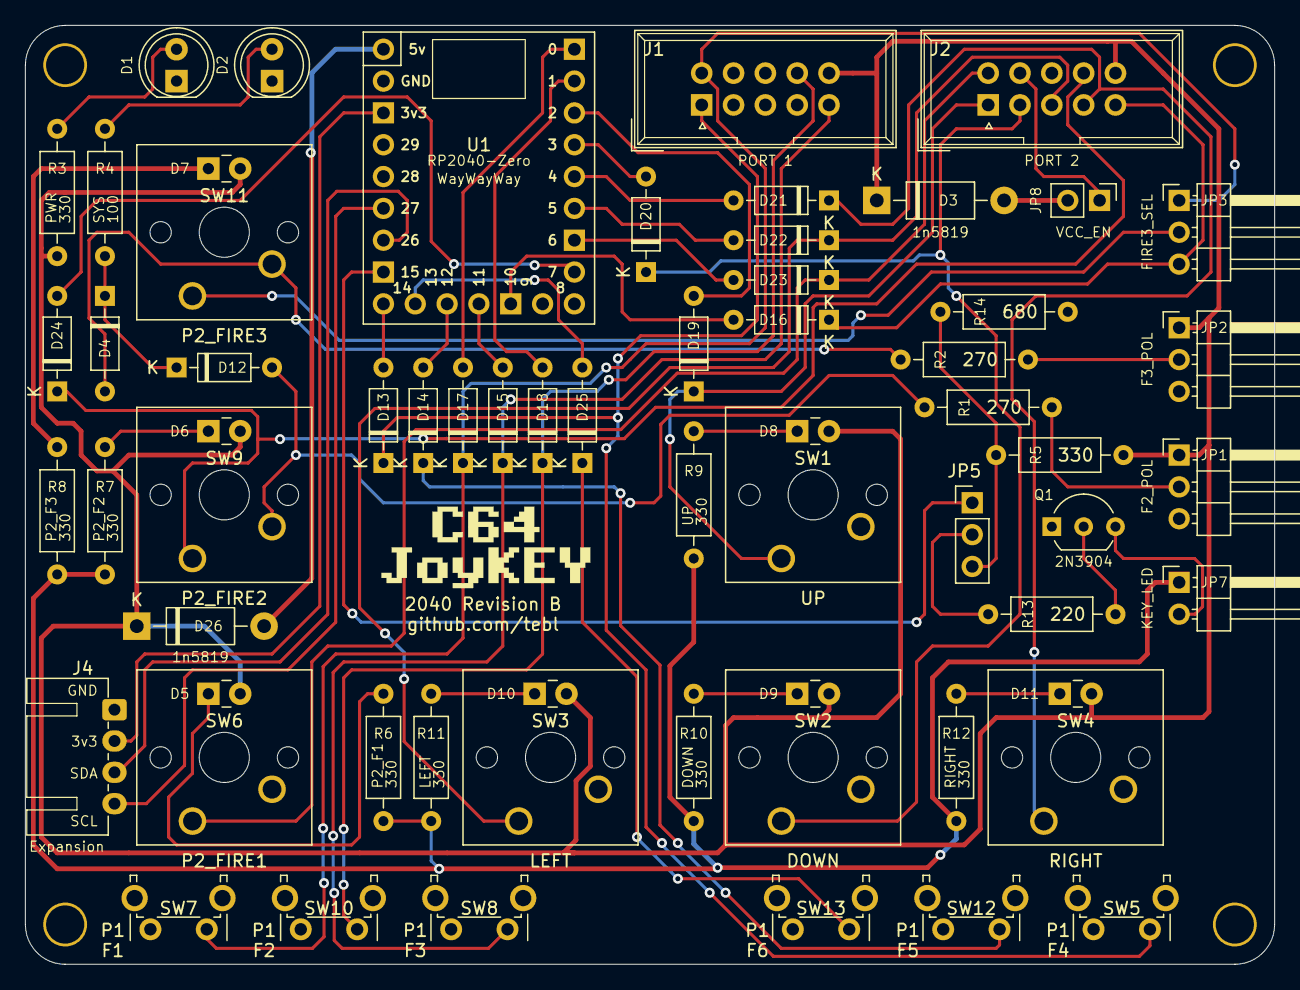
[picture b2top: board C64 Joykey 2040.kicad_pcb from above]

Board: 2 copper layers, 99.7 x 74.9 mm, 68 parts (0 on the bottom side), 55 nets.

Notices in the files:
Arcade 2040/Arcade 2040.kicad_pcb:
Licensed under
CERN OHL v1.2
